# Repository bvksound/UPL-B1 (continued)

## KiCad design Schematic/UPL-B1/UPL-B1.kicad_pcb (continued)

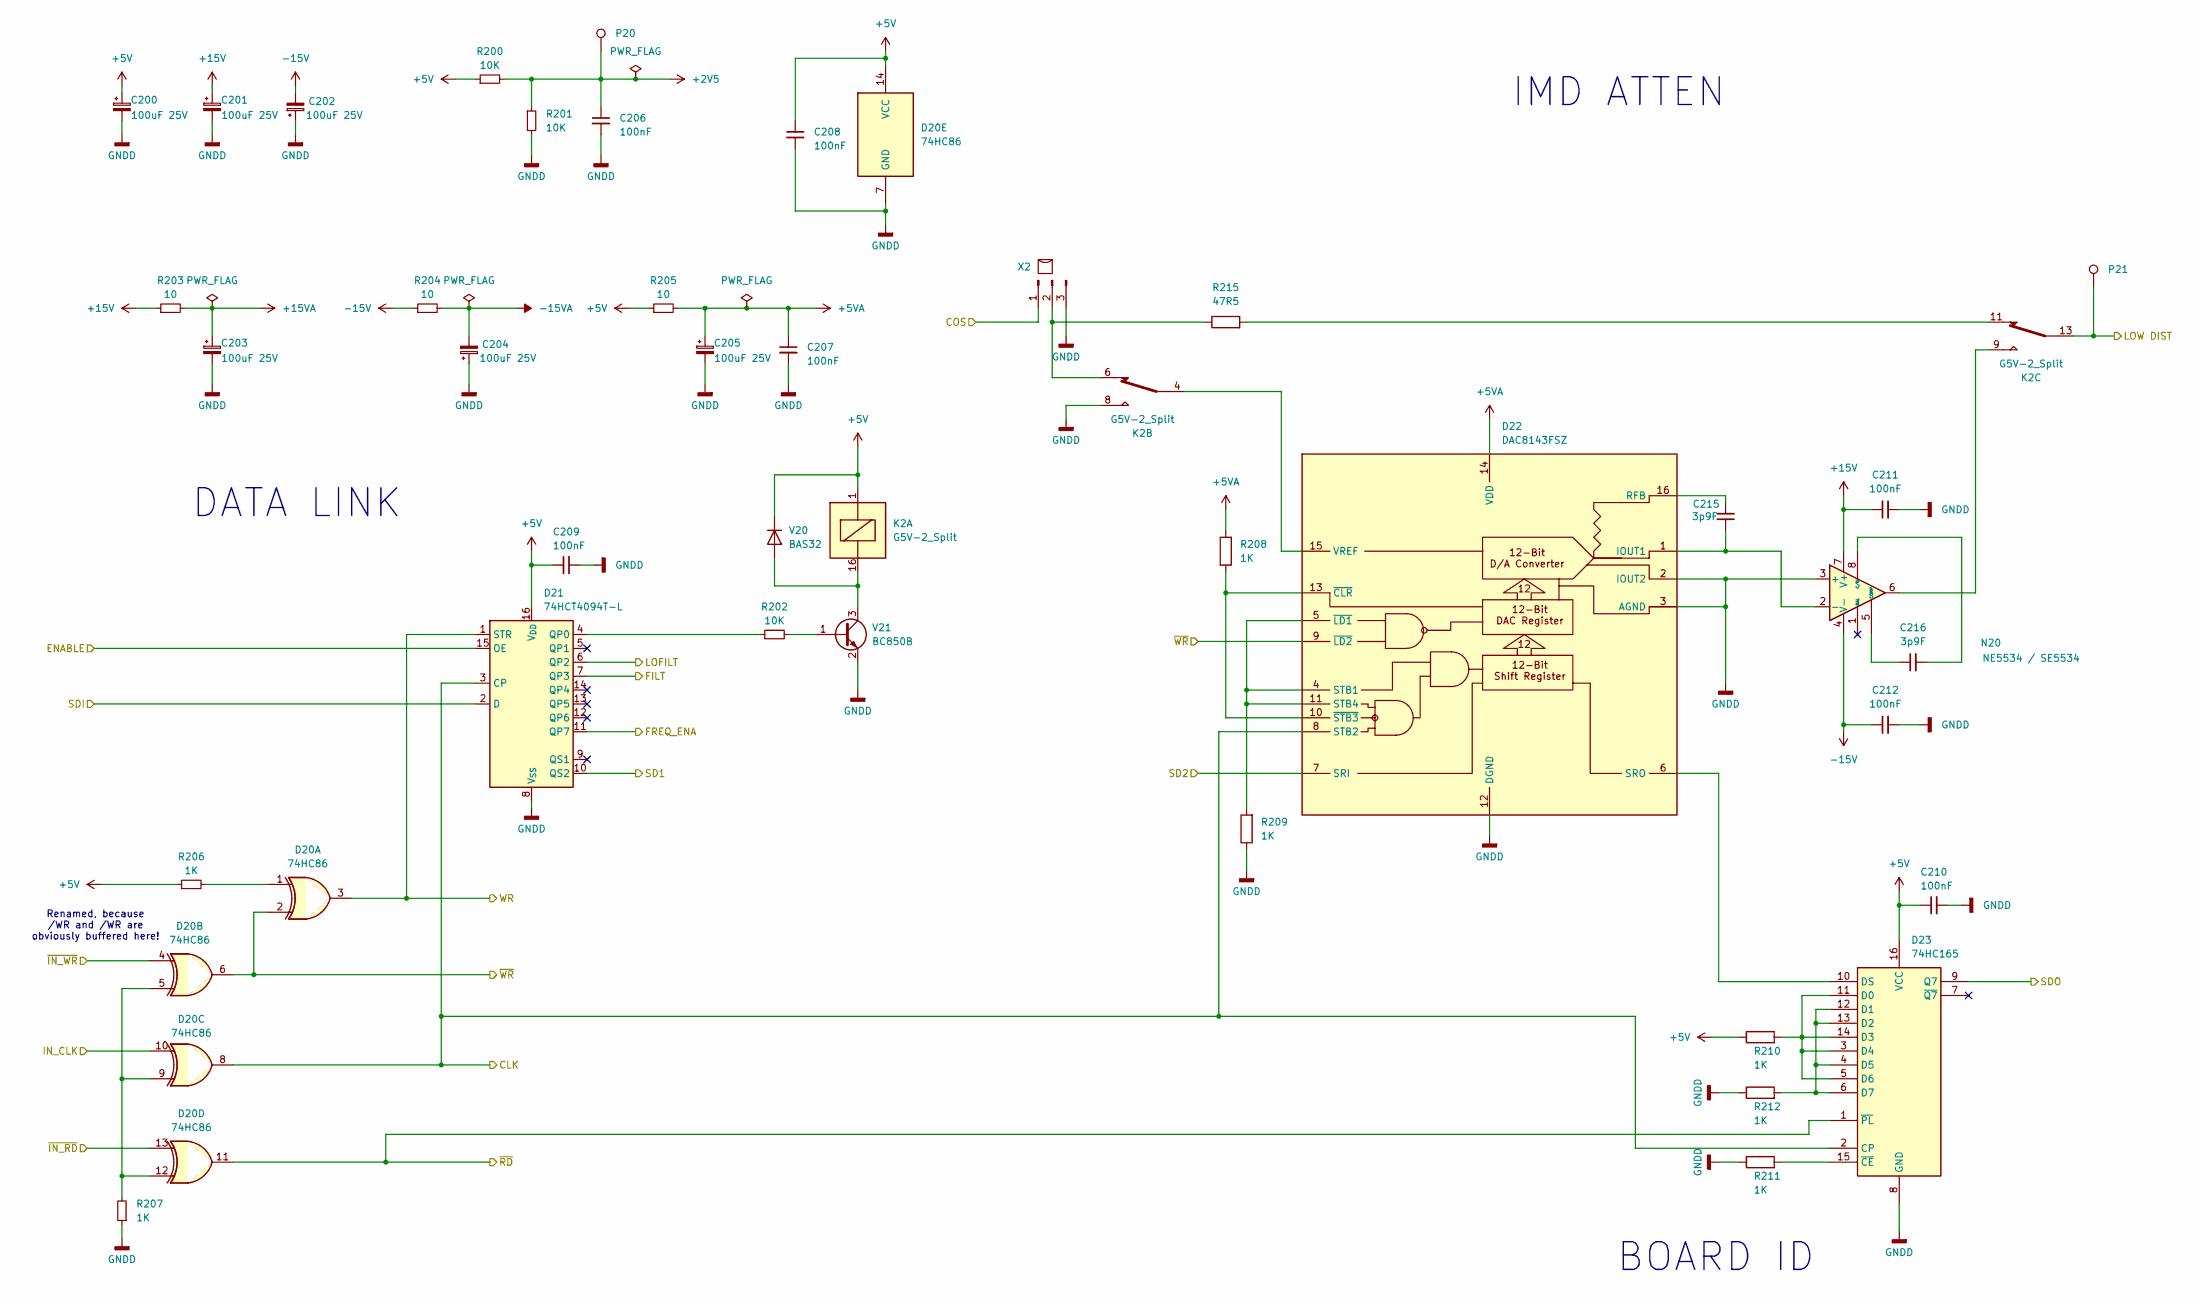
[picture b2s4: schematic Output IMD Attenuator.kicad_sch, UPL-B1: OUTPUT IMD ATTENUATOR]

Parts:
C200, C201, C202, C203, C204, C205: 100uF 25V; C_Radial_D6.3mm_H11.0mm_P2.50mm
C206, C207, C208, C209, C210, C211, C212: 100nF; C_1206_3216Metric_Pad1.33x1.80mm_HandSolder
C215, C216: 3p9F; C_1206_3216Metric_Pad1.33x1.80mm_HandSolder
D20: 74HC86; SOIC-14_3.9x8.7mm_P1.27mm
D21: 74HCT4094T-L; SOIC-16_3.9x9.9mm_P1.27mm
D22: DAC8143FSZ; SOIC-16W_7.5x10.3mm_P1.27mm
D23: 74HC165; SOIC-16_3.9x9.9mm_P1.27mm
K2: G5V-2_Split; Relay_DPDT_Omron_G5V-2
N20: NE5534 / SE5534; SOIC-8_3.9x4.9mm_P1.27mm
P20, P21: TestPoint; PinHeader_1x01_P1.00mm_Vertical
R200, R201, R202: 10K; R_1206_3216Metric_Pad1.30x1.75mm_HandSolder
R203, R204, R205: 10; R_1206_3216Metric_Pad1.30x1.75mm_HandSolder
R206, R207, R208, R209, R210, R211, R212: 1K; R_1206_3216Metric_Pad1.30x1.75mm_HandSolder
R215: 47R5; R_1206_3216Metric_Pad1.30x1.75mm_HandSolder
V20: BAS32; D_SOD-523
V21: BC850B; SOT-23
X2: Conn_01x03_Pin_Bridge; PinHeader_1x03_P2.54mm_Vertical

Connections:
+2V5: C206.1, P20.1, R200.2, R201.1; also elsewhere on the board
+5V: C200.1, C208.1, C209.1, C210.1, D20.14 (VCC), D21.16 (V_{DD}), D23.16 (VCC), K2.1, R200.1, R205.1, R206.1, R210.1, V20.1 (K); also elsewhere on the board
+5VA: C205.1, C207.1, D22.14 (VDD), R205.2, R208.2; also elsewhere on the board
+15V: C201.1, C211.1, N20.7 (V+), R203.1; also elsewhere on the board
+15VA: C203.1, R203.2; also elsewhere on the board
-15V: C202.2, C212.1, N20.4 (V-), R204.1; also elsewhere on the board
-15VA: C204.2, R204.2; also elsewhere on the board
/CLK: D20.8, D21.3 (CP), D22.8 (STB2), D23.2 (CP); also elsewhere on the board
/COS: X2.1; also elsewhere on the board
/ENABLE: D21.15 (OE); also elsewhere on the board
/IN_CLK: D20.10; also elsewhere on the board
/Integrator 1 & Loop Inverter/SD2: D22.7 (SRI); also elsewhere on the board
/LOW_DIST: K2.13, P21.1; also elsewhere on the board
/Level Control (ALC)/FILT: D21.7 (QP3); also elsewhere on the board
/Level Control (ALC)/FREQ_ENA: D21.11 (QP7); also elsewhere on the board
/Level Control (ALC)/LOFILT: D21.6 (QP2); also elsewhere on the board
/SD1: D21.10 (QS2); also elsewhere on the board
/SDI: D23.9 (Q7); also elsewhere on the board
/SDO: D21.2 (D); also elsewhere on the board
/WR: D20.3, D21.1 (STR); also elsewhere on the board
//IN_RD: D20.13; also elsewhere on the board
//IN_WR: D20.4; also elsewhere on the board
/~RD: D20.11, D23.1 (~PL); also elsewhere on the board
/~WR: D20.2, D20.6, D22.9 (~LD2); also elsewhere on the board
GNDD: C200.2, C201.2, C202.1, C203.2, C204.1, C205.2, C206.2, C207.2, C208.2, C209.2, C210.2, C211.2, C212.2, D20.7 (GND), D21.8 (V_{SS}), D22.2 (IOUT2), D22.3 (AGND), D22.12 (DGND), D23.8 (GND), K2.8, N20.3 (+), R201.2, R207.1, R209.1, R211.1, R212.1, V21.2 (E), X2.3; also elsewhere on the board
unnamed: D20.1, R206.2
unnamed: D20.5, D20.9, D20.12, R207.2
unnamed: D21.4 (QP0), R202.1
unnamed: C215.1, D22.1 (IOUT1), N20.2 (-)
unnamed: C215.2, D22.16 (RFB)
unnamed: D22.6 (SRO), D23.10 (DS)
unnamed: D22.4 (STB1), D22.5 (~LD1), D22.11 (STB4), R209.2
unnamed: D22.15 (VREF), K2.4
unnamed: D22.10 (~STB3), D22.13 (~CLR), R208.1
unnamed: D23.3 (D4), D23.5 (D6), D23.11 (D0), D23.14 (D3), R210.2
unnamed: D23.4 (D5), D23.6 (D7), D23.12 (D1), D23.13 (D2), R212.2
unnamed: D23.15 (~CE), R211.2
unnamed: K2.9, N20.6
unnamed: K2.11, R215.2
unnamed: C216.1, N20.5 (COMP)
unnamed: C216.2, N20.8 (C/B)
unnamed: K2.16, V20.2 (A), V21.3 (C)
unnamed: R202.2, V21.1 (B)
unnamed: K2.6, R215.1, X2.2

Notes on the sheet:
Renamed, because /WR and /WR are obviously buffered here!
IMD ATTEN
BOARD ID
DATA LINK

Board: 4 copper layers, 302 parts (228 on the bottom side), 200 nets, no tracks yet.

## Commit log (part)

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2025-11-23 1st commit with base information
2025-11-23 Draft kicad project added
2025-11-23 Connections page added
2025-11-24 added connections and library
2025-11-25 Integrator 2 schematic added
2025-12-07 Added Integrator 1 and Level control
2025-12-08 Add device datasheets, begin migration to hierarchical labels
2025-12-08 Begin drawing IMD section
2025-12-08 Add annotations to determine bodges
2025-12-08 update on Output IMD
2025-12-08 Prevent git from committing lock files, which I guess we don't want
2025-12-08 IMD Atten added
2025-12-08 updated to hierarchical labels
2025-12-08 Cleanup component names
2025-12-08 Added Todo on Root page
2025-12-08 Begun tracing out the original outline and placement
2025-12-08 Add topside components
2025-12-09 Add drawing of topside mechanical.
    To be used in board outline and drill patterns
2025-12-09 Begin PCB outline and add fencing drawing
2025-12-09 Minor fixups for layout.
    Reannotate, deduplicate N53B. Add some hierachical pins. First
    preparations for layout
2025-12-09 Begin redrawing overview page.
    Having a huge bitmap in the background makes KiCad lag significantly, so
    try to get rid of it.
2025-12-09 Redraw block diagram as vector art. Add more links in hierarchical overview.
    Remove original picture
2025-12-09 Clean up overview some more
2025-12-09 updated DXF files for PCB
2025-12-10 Begin making original BOM machine readable
2025-12-10 Continue BOM
2025-12-10 Add symbol for DAC8143
2025-12-10 More BOM work
2025-12-10 Even more BOM work
2025-12-10 Updated symbols for ADC and Shiftregister
2025-12-11 Group functional blocks in ALC. Begin documenting digital chain.
    Fixed D21 designator, placed a few NC-Crosses on unused pins for good
    practice.
2025-12-11 updated root schematic, added connections and removed connectorsheet
2025-12-11 Rework digital signal chain
2025-12-11 More BOM work..
2025-12-11 added majority of footprints
2025-12-12 First round of autoplacement.
2025-12-12 Some BOM work.
2025-12-12 Rough component outline on PCB
2025-12-14 Bracket added
2025-12-16 ERC fixes.
    - Power flags added for power nets "hanging" off resistors.
    - Add missing NC-markers for intentionally unconnected parts
    - Fix -15V bridge between circuits on S4/S3
    - Add +5 to /CLR of DAC
    - Use non-hierachical labels on main sheet.
2025-12-16 Use +/-15VA for some opamps and +5VA for the DACs.
    Note: Did they really use +/-15VA (denoted with asterisk in R&S
    schematics) on N34 but not on N20?
2025-12-16 Minor readability changes
2025-12-21 Updated PCB layout to include copper zones
2025-12-21 update on PCB board
2025-12-21 rough part outline
2025-12-26 added dxf files for Kicad and some documentation
2025-12-29 renamed sheets and updated main connector
2025-12-30 updated 3D-file for connector
2026-05-21 Initial version of testing Jig subproject
2026-05-21 More PSU work
2026-05-26 Add CPU and level shifter
2026-06-02 Rework connector to be alternating left/right.
2026-06-03 First iteration tester design
2026-06-03 Build a reference for SPI chains
2026-06-04 Annotate with reverse engineering clues
2026-06-04 Make +24V actually +20V as the UPL does
2026-06-11 Calculate power requirements and heat sinks.
2026-06-11 Make board production ready.
    - Fix all DRC errors (accept if need)
    - Fix all ERC errors (accept if needed)
    - Use correct 34 (!) pin connector on board
2026-06-11 First steps creating some exercising code for the B1
2026-06-12 Last fixes before production of Rev A.
    - Add signal line for SDO1 which had a break in the schematic.
    - Route out said signal
